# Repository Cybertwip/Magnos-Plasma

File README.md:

# MAGNOS // Interstellar Flight Deck — Plasma Pressure Engine v2

This build is the requested second revision of the Solar Slingshot / Alpha Centauri simulator.

## What changed

### Arrival is now a hard mission-clock hold

When a direct planetary transfer completes or the spacecraft reaches the Alpha Centauri A/B range:

- the mission physics accumulator is cleared;
- Solar-System simulation time stops advancing;
- Earth-frame and traveler clocks stop advancing;
- the UI enters `ARRIVED / HOLD` state;
- pressing **Play** does not resume time;
- only a **successfully planned new departure** releases the hold.

An invalid departure request does not release the arrival hold.

### Earth → Alpha Centauri no longer terminates at Neptune

Alpha Centauri A/B is now the default target.

Planetary encounters are optional energy/trajectory assists. After the final usable assist, the spacecraft immediately transitions to continuous interstellar plasma cruise. If a powered assist misses its target Hill sphere, the Alpha mission continues as a direct plasma injection instead of terminating.

The interstellar rendering scale activates just beyond Neptune so the UI visibly transitions from the Solar System to the Alpha Centauri leg rather than appearing to stop at Neptune.

### Futuristic bar-based cockpit

The large configuration grid has been removed from the primary UI. The cockpit now emphasizes:

- navigation-range bar;
- speed / light-speed-fraction bar;
- propellant reserve bar;
- Magnos-voltage bar;
- compact flight telemetry;
- five thermal bars;
- frozen-arrival indicator.

Only mission routing, view/simulation rate, and the Magnos plasma-engine bus are exposed as normal controls.

### Magnos schematic calibration

The included `reference/magnos-plasma.kicad_sch` is used as the design reference.

The simulator represents:

- 5 V / 1 A as the annotated source ceiling;
- the schematic's `~30KVAC ... 250Hz` node as the baseline high-voltage reference;
- 30 kVAC RMS as about 42.43 kV peak for a sine wave;
- the schematic's `target 1e+07 V / TBD` booster annotation as a selectable **hypothetical** 10 MV target ceiling.

The 87 mA text on the 30 kVAC node is not treated as power available from a 5 V / 1 A source. The Magnos voltage-ratio envelope remains power-conserving unless another energy source is modeled.

## Plasma pressure engine

The continuous open-nozzle engine still uses:

`p_e = n k_B (T_e + T_i)`

`F = mdot * v_e + p_e * A_e` with ambient pressure `p_a = 0`.

The v2 interstellar feed is a fixed hydrogen plasma mission reserve rather than a cockpit slider. Exhaust speed combines the magnetic-nozzle baseline with the relativistic speed corresponding to the selected singly-charged hydrogen accelerator voltage. The engine remains limited by available beam power, thermal rejection, finite propellant, and the open-exhaust requirement.

No open exhaust or no remaining propellant means zero sustained plasma thrust.

## Run

Serve the folder over HTTP because the simulator uses ES modules:

```bash
python3 -m http.server 8000
```

Then open `http://localhost:8000/`.

`vendor/three.mjs` is a thin wrapper around the pinned Three.js CDN module, so the browser needs network access unless you replace it with a local Three.js ES module.

## Tests

No npm dependencies are required for the model/regression tests:

```bash
node tests/plasma-pressure-engine.test.mjs
node tests/magnos-booster.test.mjs
node tests/mission-regression.test.mjs
```

## Scope

This is a reduced-order educational simulator. The included KiCad schematic is a reference artifact; the simulator does not provide high-voltage construction instructions, insulation design, component certification, or a claim that the TBD voltage targets are verified hardware ratings.

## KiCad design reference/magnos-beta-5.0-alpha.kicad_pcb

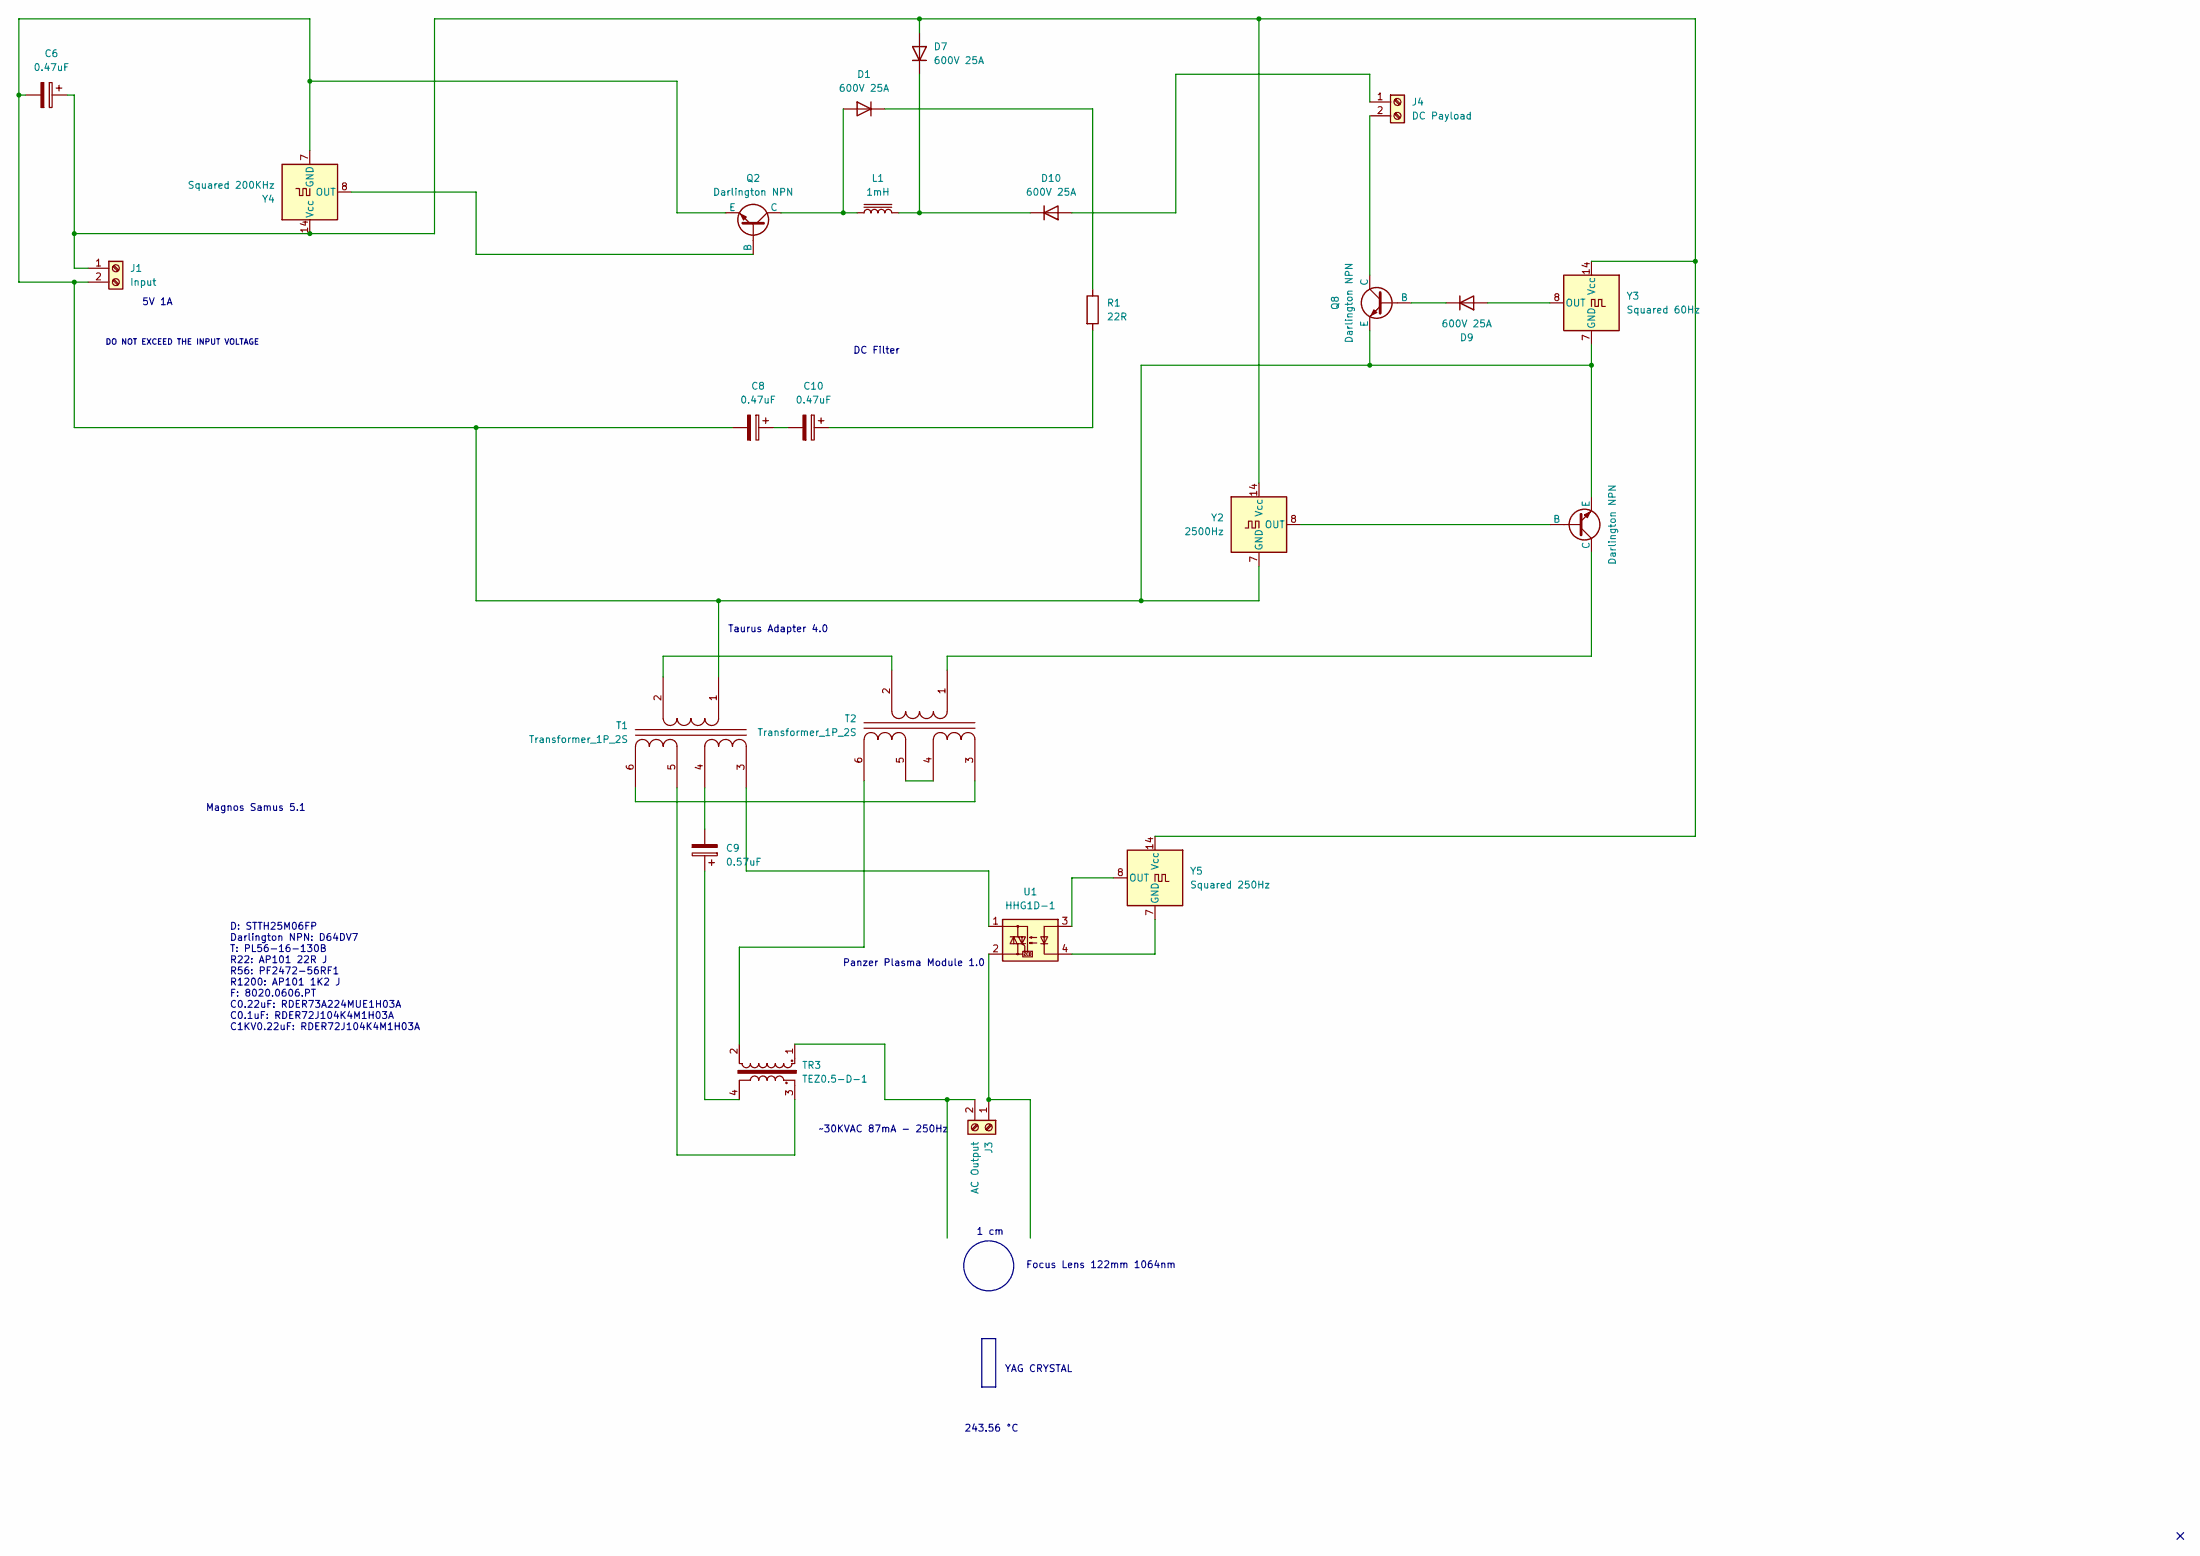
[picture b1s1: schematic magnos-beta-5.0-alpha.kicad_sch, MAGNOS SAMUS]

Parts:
C6, C8, C10: 0.47uF; C_0805_2012Metric; Mfg Part # CC0805KRX7R9BB104
C9: 0.57uF; C_0805_2012Metric; Mfg Part # CC0805KRX7R9BB104
D1, D7, D9, D10: 600V 25A; D_SMA; Mfg Part # SMA2J53CA
J1: Input; TerminalBlock_Phoenix_MKDS-1,5-2-5.08_1x02_P5.08mm_Horizont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; Mfg Part # 1757026
J3: AC Output; TerminalBlock_Phoenix_MKDS-1,5-2-5.08_1x02_P5.08mm_Horizont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; Mfg Part # 1757026
J4: DC Payload; TerminalBlock_Phoenix_MKDS-1,5-2-5.08_1x02_P5.08mm_Horizont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; Mfg Part # 1757026
L1: 1mH; L_Bourns_SRR1260; Mfg Part # SRR1260-100M
Q2, Q5, Q8: Darlington NPN; SOT-23; Mfg Part # BC817-25
R1: 22R; R_0805_2012Metric; Mfg Part # RC0805FR-0756RL
T1, T2: Transformer_1P_2S; Transformer_Wuerth_750315371
TR3: TEZ0.5-D-1; SMDIP-4_W7.62mm
U1: HHG1D-1; Relay_NCR_HHG1D-1
Y2: 2500Hz; Oscillator_DIP-14
Y3: Squared 60Hz; Oscillator_DIP-14
Y4: Squared 200KHz; Oscillator_DIP-14
Y5: Squared 250Hz; Oscillator_DIP-14

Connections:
unnamed: C9.1, TR3.4
unnamed: C10.1, R1.2
unnamed: C8.1, C10.2
unnamed: D1.2 (A), L1.1, Q2.1 (C)
unnamed: D1.1 (K), R1.1
unnamed: C6.1, D7.2 (A), J1.1, Y2.14 (Vcc), Y3.14 (Vcc), Y4.14 (Vcc), Y5.14 (Vcc)
unnamed: D9.2 (A), Y3.8 (OUT)
unnamed: D9.1 (K), Q8.2 (B)
unnamed: D10.2 (A), J4.1
unnamed: D7.1 (K), D10.1 (K), L1.2
unnamed: C6.2, C8.2, J1.2, Q2.3 (E), Q5.3 (E), Q8.3 (E), T1.1 (AA), Y2.7 (GND), Y3.7 (GND), Y4.7 (GND)
unnamed: J3.1, U1.2
unnamed: J3.2, TR3.1
unnamed: J4.2, Q8.1 (C)
unnamed: Q2.2 (B), Y4.8 (OUT)
unnamed: Q5.2 (B), Y2.8 (OUT)
unnamed: Q5.1 (C), T2.1 (AA)
unnamed: T1.2 (AB), T2.2 (AB)
unnamed: T1.3 (SA), U1.1
unnamed: C9.2, T1.4 (SB)
unnamed: T1.5 (SC), TR3.3
unnamed: T1.6 (SD), T2.3 (SA)
unnamed: T2.4 (SB), T2.5 (SC)
unnamed: T2.6 (SD), TR3.2
unnamed: U1.4, Y5.7 (GND)
unnamed: U1.3, Y5.8 (OUT)

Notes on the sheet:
Taurus Adapter 4.0
~30KVAC 87mA - 250Hz
Focus Lens 122mm 1064nm
DC Filter
D: STTH25M06FP Darlington NPN: D64DV7 T: PL56-16-130B R22: AP101 22R J R56: PF2472-56RF1 R1200: AP101 1K2 J F: 8020.0606.PT C0.22uF: RDER73A224MUE1H03A C0.1uF: RDER72J104K4M1H03A C1KV0.22uF: RDER72J104K4M1H03A
243.56 °C
5V 1A
DO NOT EXCEED THE INPUT VOLTAGE
Panzer Plasma Module 1.0
YAG CRYSTAL
Magnos Samus 5.1
1 cm

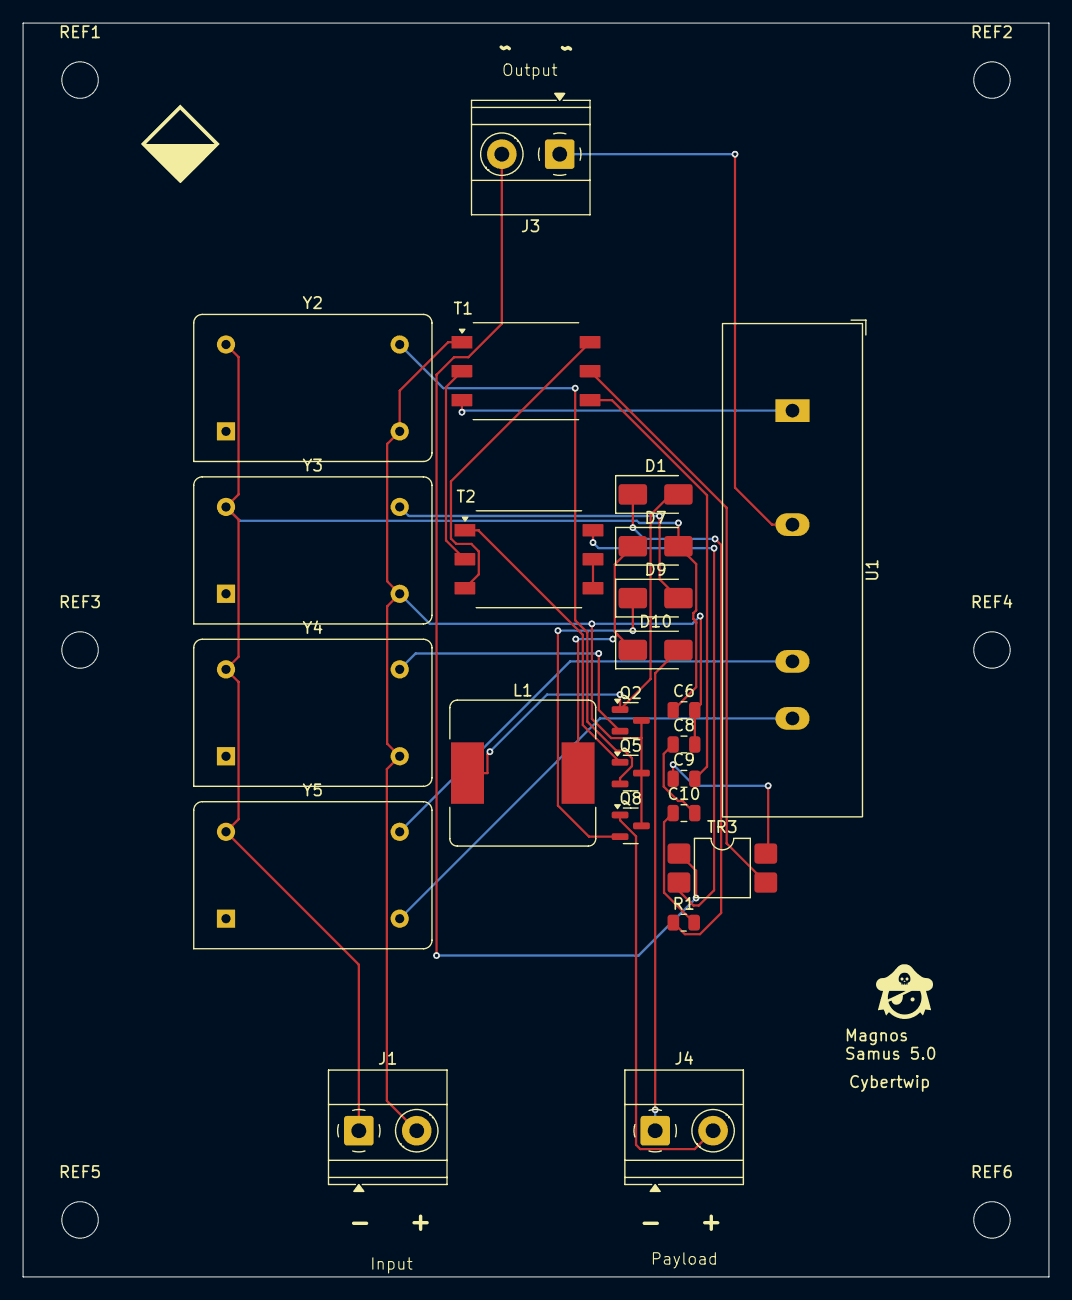
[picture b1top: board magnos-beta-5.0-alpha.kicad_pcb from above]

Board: 2 copper layers, 90.0 x 110.0 mm, 32 parts (0 on the bottom side), 26 nets.

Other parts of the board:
G1, G2: LOGO
REF1: MH1; MountingHole_3.2mm_M3
REF2: MH2; MountingHole_3.2mm_M3
REF3, REF5: MH3; MountingHole_3.2mm_M3
REF4, REF6: MH4; MountingHole_3.2mm_M3
